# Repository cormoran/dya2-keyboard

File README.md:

# <picture><source srcset="docs/public/dya-dark.svg" media="(prefers-color-scheme: dark)"> DYA2 Split Keyboard

Hardware designs are under preparation for publish...

## License

- DYA logo <picture><source srcset="docs/public/dya-dark.svg" media="(prefers-color-scheme: dark)">: All rights reserved.
- Other keyboard picture : CC BY
- Hardware
  - kicad library (./hardware/kicad_library/\*) and sch (\*.kicad_sch): MIT
  - PCB (\*.kicad_pcb): **CC BY-NC**
  - Case data (\*.stl): CC BY
- Documents
  - All pictures+ CC BY
  - Other source codes: MIT

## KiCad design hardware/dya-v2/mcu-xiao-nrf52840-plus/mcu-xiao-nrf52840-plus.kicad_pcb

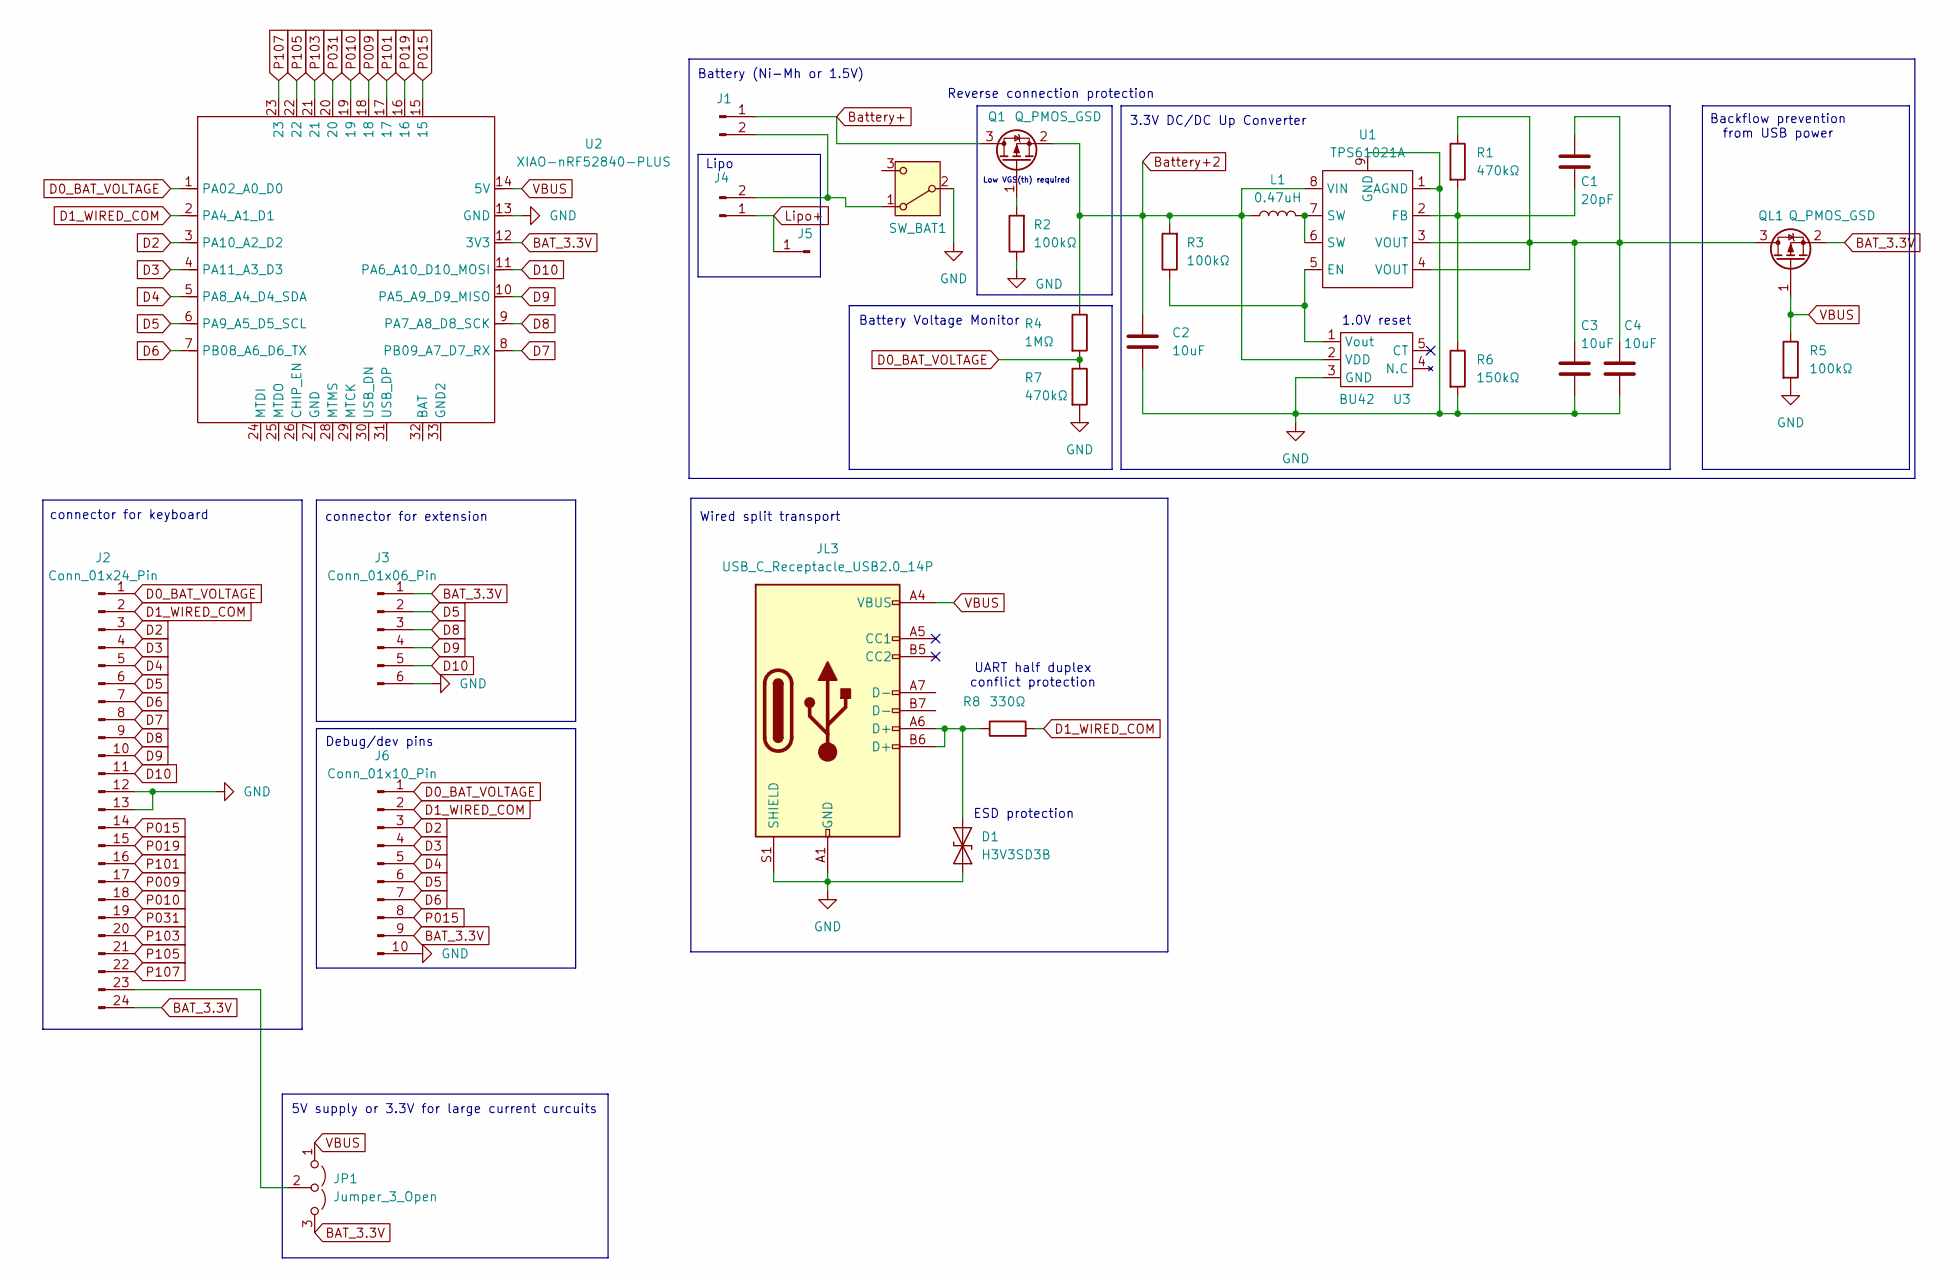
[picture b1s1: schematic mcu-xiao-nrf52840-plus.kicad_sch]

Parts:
C1: 20pF; C_0805_2012Metric; LCSC C1798
C2, C3, C4: 10uF; C_0805_2012Metric; LCSC C15850
D1: H3V3SD3B; D_SOD-323; LCSC C20615802
J1: Conn_01x02_Pin; JST_PH_S2B-PH-K_1x02_P2.00mm_Horizontal; LCSC C173752
J2: Conn_01x24_Pin; HIROSE-FH34SRJ-24S-0.5SH; LCSC C324726
J3: Conn_01x06_Pin; JUSHUO-AFH34-S06FIA-1H; LCSC C224194
J4: Conn_01x02_Pin; JST_PH_S2B-PH-K_1x02_P2.00mm_Horizontal
J5: Conn_01x01_Pin; SolderWire-0.25sqmm_1x01_D0.65mm_OD1.7mm
J6: Conn_01x10_Pin; PinHeader_1x10_P1.27mm_Vertical
JL3: USB_C_Receptacle_USB2.0_14P; USB_C_ Recessed_ YTC-TC16-31_1.2mm; LCSC C2927296
JP1: Jumper_3_Open; SolderJumper-3_P1.3mm_Open_RoundedPad1.0x1.5mm
L1: 0.47uH; L_1008_2520Metric; LCSC C703140
Q1: Q_PMOS_GSD; SOT-23; LCSC C144153
QL1: Q_PMOS_GSD; SOT-23; LCSC C15127
R1, R7: 470kΩ; R_0805_2012Metric; LCSC C17709
R2, R3, R5: 100kΩ; R_0805_2012Metric; LCSC C149504
R4: 1MΩ; R_0805_2012Metric; LCSC C17514
R6: 150kΩ; R_0805_2012Metric; LCSC C17470
R8: 330Ω; R_0805_2012Metric; LCSC C17630
SW_BAT1: SW_SPDT; SSSS811101; LCSC C109335
U1: TPS61021A; WSON-8-1EP_2x2mm_P0.5mm_EP0.9x1.6mm; LCSC C193037
U2: XIAO-nRF52840-PLUS; XIAO_nRF52840_plus_hybrid
U3: BU42; BU42XX; LCSC C2066584

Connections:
BAT_3.3V: J2.24, J3.1, J6.9, JP1.3 (B), QL1.2 (S), U2.12 (3V3)
Battery+: J1.1, Q1.3 (D)
Battery+2: C2.1, L1.1, Q1.2 (S), R3.2, R4.1, U1.8 (VIN), U3.2 (VDD)
D0_BAT_VOLTAGE: J2.1, J6.1, R4.2, R7.1, U2.1 (PA02_A0_D0)
D1_WIRED_COM: J2.2, J6.2, R8.2, U2.2 (PA4_A1_D1)
D2: J2.3, J6.3, U2.3 (PA10_A2_D2)
D3: J2.4, J6.4, U2.4 (PA11_A3_D3)
D4: J2.5, J6.5, U2.5 (PA8_A4_D4_SDA)
D5: J2.6, J3.2, J6.6, U2.6 (PA9_A5_D5_SCL)
D6: J2.7, J6.7, U2.7 (PB08_A6_D6_TX)
D7: J2.8, U2.8 (PB09_A7_D7_RX)
D8: J2.9, J3.3, U2.9 (PA7_A8_D8_SCK)
D9: J2.10, J3.4, U2.10 (PA5_A9_D9_MISO)
D10: J2.11, J3.5, U2.11 (PA6_A10_D10_MOSI)
GND: C2.2, C3.2, C4.2, D1.2 (A2), J2.12, J2.13, J3.6, J6.10, JL3.A1 (GND), JL3.A12 (GND), JL3.B1 (GND), JL3.B12 (GND), JL3.S1 (SHIELD), R2.1, R5.2, R6.2, R7.2, SW_BAT1.2 (B), U1.1 (AGND), U1.9 (GND), U2.13 (GND), U3.3 (GND)
Lipo+: J4.1, J5.1
unnamed: D1.1 (A1), JL3.A6 (D+), JL3.B6 (D+), R8.1
unnamed: J1.2, J4.2, SW_BAT1.1 (A)
unnamed: J2.23, JP1.2 (C)
unnamed: L1.2, U1.6 (SW), U1.7 (SW)
unnamed: Q1.1 (G), R2.2
unnamed: C1.1, C3.1, C4.1, QL1.3 (D), R1.1, U1.3 (VOUT), U1.4 (VOUT)
unnamed: R3.1, U1.5 (EN), U3.1 (Vout)
unnamed: C1.2, R1.2, R6.1, U1.2 (FB)
P009: J2.17, U2.18
P010: J2.18, U2.19
P015: J2.14, J6.8, U2.15
P019: J2.15, U2.16
P031: J2.19, U2.20
P101: J2.16, U2.17
P103: J2.20, U2.21
P105: J2.21, U2.22
P107: J2.22, U2.23
VBUS: JL3.A4 (VBUS), JL3.A9 (VBUS), JL3.B4 (VBUS), JL3.B9 (VBUS), JP1.1 (A), QL1.1 (G), R5.1, U2.14 (5V)

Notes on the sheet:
connector for keyboard
1.0V reset
ESD protection
3.3V DC/DC Up Converter
Battery (Ni-Mh or 1.5V)
Reverse connection protection
Backflow prevention from USB power
Battery Voltage Monitor
Wired split transport
5V supply or 3.3V for large current curcuits
Debug/dev pins
Lipo
Low VGS(th) required
connector for extension
UART half duplex conflict protection

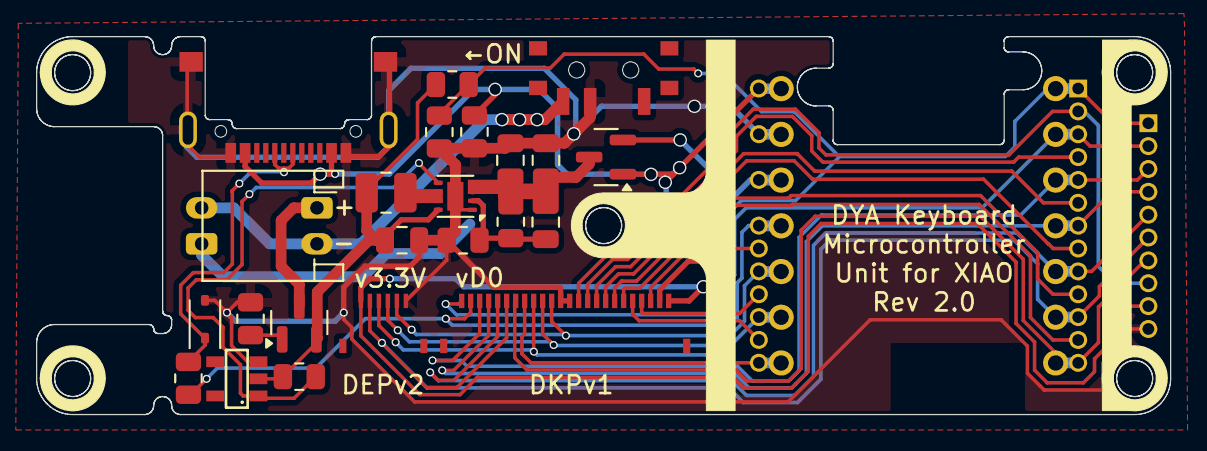
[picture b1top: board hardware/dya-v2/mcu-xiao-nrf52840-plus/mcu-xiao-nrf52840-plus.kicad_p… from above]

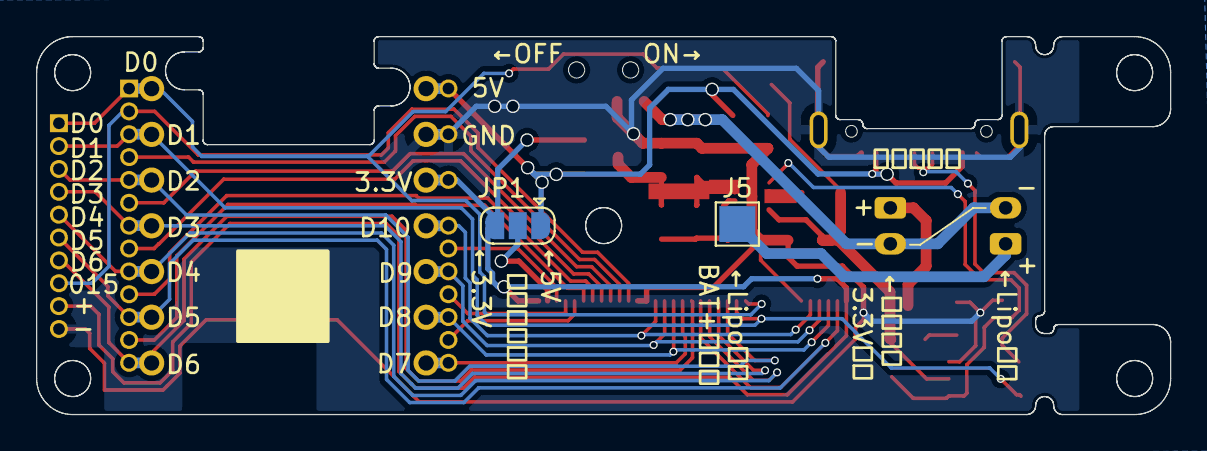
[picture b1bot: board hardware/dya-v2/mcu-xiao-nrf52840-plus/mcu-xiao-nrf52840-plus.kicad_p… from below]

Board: 2 copper layers, 63.0 x 21.0 mm, 28 parts (3 on the bottom side), 34 nets.

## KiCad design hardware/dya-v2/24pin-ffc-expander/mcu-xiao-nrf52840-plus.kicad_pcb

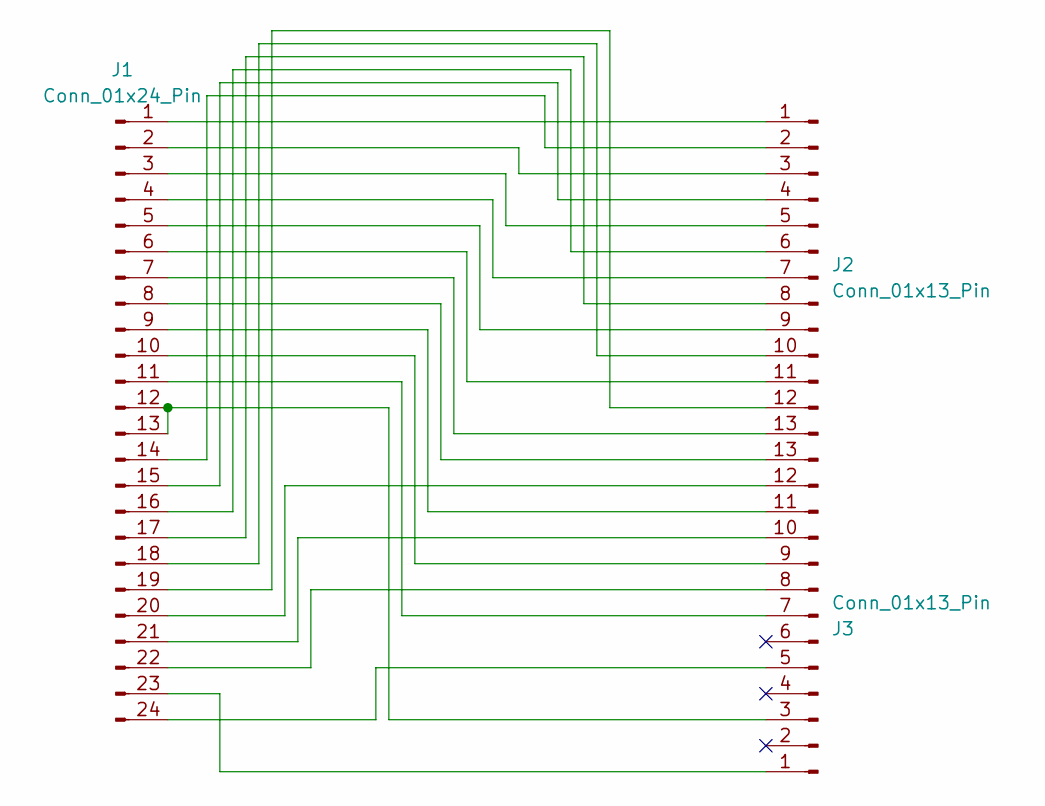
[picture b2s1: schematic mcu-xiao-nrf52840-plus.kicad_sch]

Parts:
J1: Conn_01x24_Pin; HIROSE-FH34SRJ-24S-0.5SH; LCSC C324726
J2, J3: Conn_01x13_Pin; PinHeader_1x13_P1.27mm_Vertical

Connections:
unnamed: J1.1, J2.1
unnamed: J1.2, J2.3
unnamed: J1.3, J2.5
unnamed: J1.4, J2.7
unnamed: J1.5, J2.9
unnamed: J1.6, J2.11
unnamed: J1.7, J2.13
unnamed: J1.8, J3.13
unnamed: J1.9, J3.11
unnamed: J1.10, J3.9
unnamed: J1.11, J3.7
unnamed: J1.12, J1.13, J3.3
unnamed: J1.14, J2.2
unnamed: J1.15, J2.4
unnamed: J1.16, J2.6
unnamed: J1.17, J2.8
unnamed: J1.18, J2.10
unnamed: J1.19, J2.12
unnamed: J1.20, J3.12
unnamed: J1.21, J3.10
unnamed: J1.22, J3.8
unnamed: J1.23, J3.1
unnamed: J1.24, J3.5

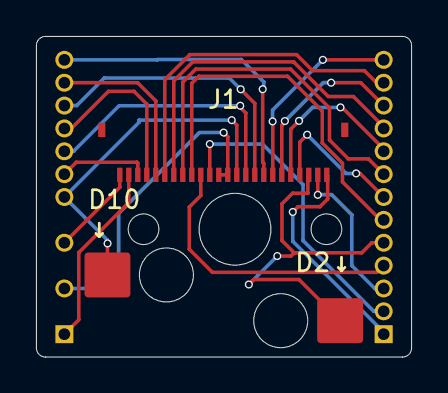
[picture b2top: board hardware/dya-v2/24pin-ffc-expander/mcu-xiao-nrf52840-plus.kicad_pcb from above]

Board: 2 copper layers, 20.8 x 17.8 mm, 3 parts (0 on the bottom side), 23 nets.

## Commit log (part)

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2026-01-12 Initialize docs with astro starlight
2026-01-12 Add document contents
2026-02-19 Draft build guide
2026-02-20 Build guide initial version
2026-02-20 Add react dependency
2026-02-21 Refine build guide
2026-02-21 google analysis and some fix
2026-02-21 Add github actions to deploy docs
2026-02-21 Add readme, license
2026-02-21 Fix build error
2026-02-21 Improve dark mode support
2026-02-21 Dark mode log in readme
2026-02-21 Add og and locale setting
2026-02-22 Fix firmware and keymap description for DYA2
2026-02-23 ソケットのはんだ不良関連情報を追加
2026-02-24 Add link to case data
2026-02-24 Improve usage guide and customization
2026-03-05 Add cautions when assembly
2026-03-17 Add more note about ball color
2026-03-27 Add stabilizer
2026-03-27 Add ffc expander and xiao expander circuit
2026-03-27 Update docs related to XIAO reset switch
2026-03-28 Add support for keyket
